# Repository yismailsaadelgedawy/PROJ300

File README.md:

# 32-bit ARM Inspired FPGA Computer

## Introduction

Here, you will find some media to showcase the workings/features of the project.
For detail on how all of this works, see my LinkedIn profile post at: [https://www.linkedin.com/in/youssef-el-geddawy-ab2085292/](https://www.linkedin.com/feed/update/urn:li:activity:7228014319110664192/)

### Overall System Running

https://github.com/user-attachments/assets/22ee120e-133d-488a-b780-022c8d299afa

Green LEDs: general purpose registers, r0-r12.
Red LEDs: memory mapped registers.

The assembly program running is the following:

```
str(0x01, vga_sel); // manual rendering mode
mov(r0, 0x000); // r0 init - colour data
str(0, tmr); // make sure timer is stopped
str(r0, vga_colour);
str(70, tmr); // tmr start 70ms
ldr(r1, "[]", tmr); // tmr state
cmp(r1, 1); // is timer done
beq(9); // if
b(5); // else
add(r0, r0,1);   
add(r1, r1,2);   
add(r2, r2,3);   
add(r3, r3,7);   
add(r4, r4,15);   
add(r5, r5,31);   
add(r6, r6,63);   
add(r7, r7,127);   
add(r8, r8,255);   
add(r9, r9,511);
add(r10, r10,1023);
add(r11, r11,2047);
add(r12, r12,4095);
str(r0, led); // leds on
b(2); // back to start

// showcase program //
```

### Keyboard Piano

https://github.com/user-attachments/assets/b63c3ae4-20a9-44ec-8537-4e127ff7aa50

The assembly program running is the following:

```
str(0x01, vga_sel); // manual rendering mode
ldr(r0, "[]", keyboard_input); // read key pressed
cmp(r0, 0x1C); // A
beq(5); // if
b(13); // else
str(0x1C, audio); // A note
str(0xF00, vga_colour); // red
ldr(r0, "[]", keyboard_input); // read key pressed
cmp(r0, 0x00); // key released
beq(11); // if
b(7); // else
str(0x00, audio); // tune off
str(0x00, vga_colour); // display off
cmp(r0, 0x32); // B
beq(16); // if
b(24); // else
str(0x32, audio); // B note
str(0xE80, vga_colour); // orange
ldr(r0, "[]", keyboard_input); // read key pressed
cmp(r0, 0x00); // key released
beq(22); // if
b(18); // else
str(0x00, audio); // tune off
str(0x00, vga_colour); // display off
cmp(r0, 0x21); // C
beq(27); // if
b(35); // else
str(0x21, audio); // C note
str(0xFF0, vga_colour); // yellow
ldr(r0, "[]", keyboard_input); // read key pressed
cmp(r0, 0x00); // key released
beq(33); // if
b(29); // else
str(0x00, audio); // tune off
str(0x00, vga_colour); // display off
cmp(r0, 0x23); // D
beq(38); // if
b(46); // else
str(0x23, audio); // D note
str(0x0F0, vga_colour); // green
ldr(r0, "[]", keyboard_input); // read key pressed
cmp(r0, 0x00); // key released
beq(44); // if
b(40); // else
str(0x00, audio); // tune off
str(0x00, vga_colour); // display off
cmp(r0, 0x24); // E
beq(49); // if
b(57); // else
str(0x24, audio); // E note
str(0x00F, vga_colour); // blue
ldr(r0, "[]", keyboard_input); // read key pressed
cmp(r0, 0x00); // key released
beq(55); // if
b(51); // else
str(0x00, audio); // tune off
str(0x00, vga_colour); // display off
cmp(r0, 0x2B); // F
beq(60); // if
b(68); // else
str(0x2B, audio); // F note
str(0xB3E, vga_colour); // indigo
ldr(r0, "[]", keyboard_input); // read key pressed
cmp(r0, 0x00); // key released
beq(66); // if
b(62); // else
str(0x00, audio); // tune off
str(0x00, vga_colour); // display off
cmp(r0, 0x34); // G
beq(71); // if
b(1); // else
str(0x34, audio); // G note
str(0x83F, vga_colour); // violet
ldr(r0, "[]", keyboard_input); // read key pressed
cmp(r0, 0x00); // key released
beq(77); // if
b(73); // else
str(0x00, audio); // tune off
str(0x00, vga_colour); // display off
b(1);

// showcase program //
```

### Hardware Timers and Blinky

https://github.com/user-attachments/assets/cfb77016-71fe-4d39-8311-53863db17fb7

The assembly program running is the following:

```
str(0x00, led); // LEDs off initially
str(100, tmr); // start 100ms tmr
ldr(r0, "[]", tmr); // timer state
cmp(r0, 0x01);  // if done
beq(6); // if
b(2); // else
str(0xFF, led); // LEDs on
str(0x00, tmr); // stop tmr;
str(100, tmr); // start 100ms timer
ldr(r0, "[]", tmr); // timer state
cmp(r0, 0x01);  // if done
beq(13); // if
b(9); // else
str(0x00, led); // LEDs off
str(0x00, tmr); // stop tmr;
b(1);

```

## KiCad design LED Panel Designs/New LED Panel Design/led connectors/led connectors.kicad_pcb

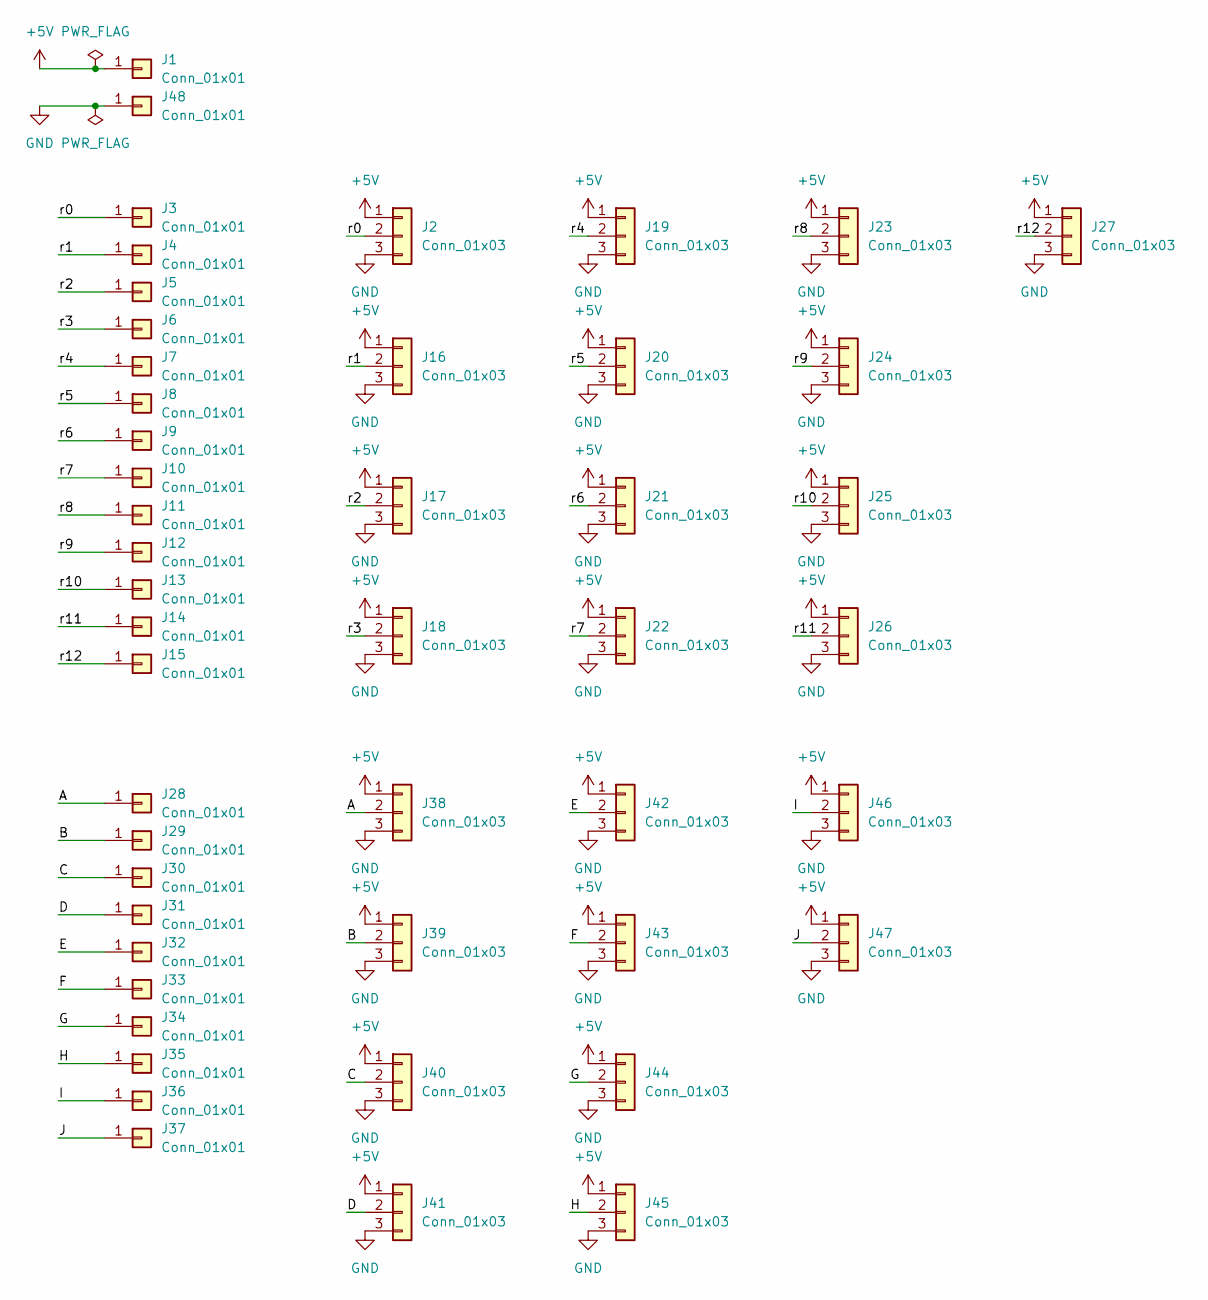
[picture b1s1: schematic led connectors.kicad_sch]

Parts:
J1, J3, J4, J5, J6, J7, J8, J9, J10, J11, J12, J13, J14, J15, J28, J29, J30, J31, J32, J33, J34, J35, J36, J37, J48: Conn_01x01; PinHeader_1x01_P2.54mm_Vertical
J2, J16, J17, J18, J19, J20, J21, J22, J23, J24, J25, J26, J27, J38, J39, J40, J41, J42, J43, J44, J45, J46, J47: Conn_01x03; JST_XH_B3B-XH-A_1x03_P2.50mm_Vertical

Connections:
+5V: J1.1, J2.1, J16.1, J17.1, J18.1, J19.1, J20.1, J21.1, J22.1, J23.1, J24.1, J25.1, J26.1, J27.1, J38.1, J39.1, J40.1, J41.1, J42.1, J43.1, J44.1, J45.1, J46.1, J47.1
/A: J28.1, J38.2
/B: J29.1, J39.2
/C: J30.1, J40.2
/D: J31.1, J41.2
/E: J32.1, J42.2
/F: J33.1, J43.2
/G: J34.1, J44.2
/H: J35.1, J45.2
/I: J36.1, J46.2
/J: J37.1, J47.2
/r0: J2.2, J3.1
/r1: J4.1, J16.2
/r2: J5.1, J17.2
/r3: J6.1, J18.2
/r4: J7.1, J19.2
/r5: J8.1, J20.2
/r6: J9.1, J21.2
/r7: J10.1, J22.2
/r8: J11.1, J23.2
/r9: J12.1, J24.2
/r10: J13.1, J25.2
/r11: J14.1, J26.2
/r12: J15.1, J27.2
GND: J2.3, J16.3, J17.3, J18.3, J19.3, J20.3, J21.3, J22.3, J23.3, J24.3, J25.3, J26.3, J27.3, J38.3, J39.3, J40.3, J41.3, J42.3, J43.3, J44.3, J45.3, J46.3, J47.3, J48.1

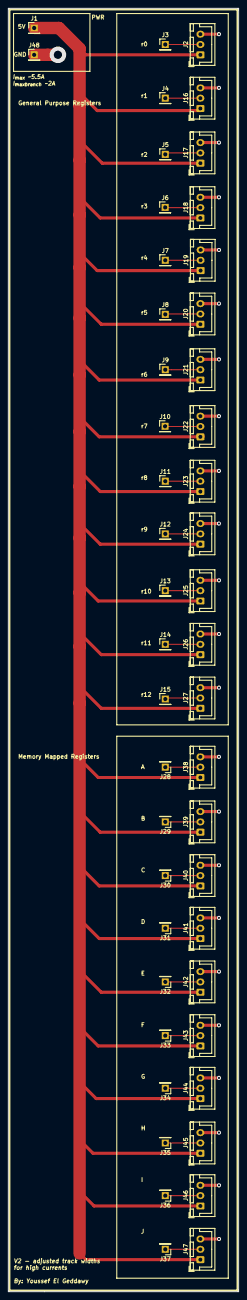
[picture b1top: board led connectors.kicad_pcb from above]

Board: 2 copper layers, 55.8 x 310.8 mm, 48 parts (0 on the bottom side), 25 nets.

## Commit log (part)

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2024-01-21 Initial file setup
2024-01-22 SD card folder
    (maybe I will do it - who knows)
2024-01-24 created LEDs folder
2024-01-30 finished hsync and vsync counters
    also added quartus project files
2024-01-30 quartus pin setup and schematic
2024-01-30 RGB controller v1 done
2024-01-31 sprite ROMs and RGB controller v2
2024-01-31 Multiple sprite support added
2024-01-31 neatened schematic
2024-01-31 added comments on schematic
2024-01-31 added comments; removed unneeded code
2024-02-01 added pixel offsets
    using signed arithmetic now
2024-02-01 removed redundant signed types
2024-02-01 adjusted bit widths to accommodate sign bit
2024-02-01 adjustments in bit widths
    will add sprite movement according to user input later -- so far sprite offsets are hardwired into the silicon
2024-02-01 created audio controller folder
2024-02-02 [NOT WORKING] attempt at code optimisation
2024-02-02 buttons move sprites now!
2024-02-02 folder name change
2024-02-02 Added Block Diagram.drawio
2024-02-02 updated block diagram
2024-02-02 added edge detection
    uses a nifty 4-pixel mechanism
2024-02-02 VGA controller complete (for now)
    tidied up schematic files
2024-02-03 neatened schematic + comments
2024-02-04 added fine tuned clock divider
    can take any frequency from 1Hz to 25MHz
2024-02-04 optimised code
    combined outputs into busses - cleaner!
2024-02-04 commented schematic
2024-02-06 created ps2 modules
    keyboard is not working; cannot test yet
2024-02-06 [BUG] ps2 module
    * added seven segment display to help debug
    * simulated holding down the same key in the tb
    * ps2 controller bugs out when holding down the same key - will fix later
2024-02-06 updated testbench for ps2 controller
2024-02-06 [BUG FIX] ps2 data no longer shifts
    *still another bug left to squash (latching issue)
2024-02-06 schematic update
2024-02-07 fixed all PS2 bugs
    works perfectly now!
2024-02-08 audio controller v1 done
    still barebones; not very well written imo
2024-02-08 added keyboard key detector
    untested still
2024-02-08 added audio files and key release detection
2024-02-09 [NOT WORKING] merged keyboard with audio controller
    will fix later
2024-02-09 adjusted bus width and frequencies
2024-02-09 [FIX] keyboard audio works now
    even sharp notes work!
2024-02-09 added lower octave switch
2024-02-09 added comments and updated schematics
2024-02-14 [UNTESTED] created UART modules
    * software to send a character on UART2
    * firmware UART components
2024-02-14 [BUG] wired up UART modules
    deadlock via "transmission_state" wire!!!!
    will fix later
2024-02-14 [FIX] UART fully working now
    still need to think about CDC...
2024-02-14 updated UART schematic
2024-02-16 added debouncer and debug address counter
    the button and its address counter will be used for instruction debugging later!
2024-02-16 renamed modules for clarity
2024-02-16 [UNTESTED] instruction RAM v1 completed
    still need to add a CPU random access fetch mode later
2024-02-16 added random access fetch template code
2024-02-17 [NOT WORKING] initial testing of RAM
2024-02-17 [NOT WORKING] almost there with RAM...
2024-02-17 removed redundant comments
2024-02-17 many bug fixes and additions
    * fixed instruction RAM
    * added variable read frequency parameter to RAM
    * add CDC via double flopping from UART to RAM
2024-02-21 added CPU design files
2024-02-21 Added ISA descriptions
2024-02-21 optimised instruction RAM
    removed FIFO read mode - unnecessary.; replaced with random access fetch (for the CPU)
    ALM utilisation went down from 10% -> 7%
2024-02-21 Reduced max number of instructions in RAM
    Reduction from 255 instructions to 100.
    Important as cannot infer BRAM.
    ALM utilisation reduced from 7% -> 4%
2024-02-22 created individual CPU components
    haven't tested them as a whole yet, just individual tests for now
2024-02-22 [async problem] connections + many bug fixes
    working in simulation but not IRL;
    asynchronous problem;
    will have to find an alternative
2024-02-23 [BUG FIX] fixed CPU
    works fine now!
    found an alternative to asynchronous load!
2024-02-23 made instructions more readable
    concatenation!
2024-02-23 added schematic comments
2024-02-28 added some arm assembly
    to approximate my CPU architecture and ISA
2024-02-28 commented the assembly
    includes utilisation
2024-02-28 started designed ISA
2024-02-28 updated ISA
2024-02-28 refined ISA
2024-02-29 draft execution routines
2024-03-01 updated ISA file
    * modified routines
    * added control signal logic
2024-03-13 MAJOR ISA update
2024-03-13 added MEMLOAD as control line in ISA
    architecture now includes bidirectional data!
2024-03-18 started coding complex CPU modules
    * ALU
    * BUS MUX
    * CU counter and decoder
    * CU logic WIP
    also fixed a few ISA bugs
2024-03-19 Update CU_logic.sv
    added control signals for most states
    a few more to go
2024-03-19 [UNTESTED] completed CU logic
    will testbench it and verify it works later!
2024-03-19 testbenched CU logic module
    all good!
2024-03-20 built NZCV logic module
    the CPU has flags now!
2024-03-20 added testbench automation using do file
    handy!
2024-03-20 added do file for CU_logic module
2024-03-21 GPR and operand selectors completed
    tested as well!
2024-03-21 added do file for GPR circuit
2024-03-21 cleaned up the do file
    uses a wildcard instead :)
2024-03-22 [HALF-TESTED] completed memory modules
    * tested all individually - pass
    * yet to test them all together
    this is regarding the encapsulation of the instruction, memory mapped regs and stack memories
2024-03-22 edited quartus files
2024-03-23 fully connected and tested memory modules
    * memory now completed
    * passes all tests
2024-03-23 made tests more rigorous; renamed files
    * encapsulated the concatenator and the rest of the GPR selection circuitry - more readable
    * renamed files to be more sensical
    * added assertions to GPR_selector_tb to make the test more rigorous!
2024-03-23 fixed comment
2024-03-23 added guide comment in case
2024-03-24 preparing CPU for testing
    * wired CPU
    * started writing instructions in test ROM
    ** major oversight discovered in AL operations; will work on a compensation mechanism later
2024-03-24 improved testing methodology
    * shown in one file
    * only display errors; use an error flag and a print statement at the end if all tests passed or not!
2024-03-25 [MAJOR UPDATE] bug fixes + module changes
    * fixed many connection errors in the schematic
    * fixed bug in CU_logic where cmp1 was missing COUNTER_CLR to go back to the fetch1 state
    * modified des_reg_selector to allow rop2 bits to pass through in the ALTMOV1 state
    * made flags_setter from FF->latch (fixes bugs)
    * modified testROM cmp instructions to be more useful in testing
    * changed some module semantics including:
2024-03-25 removed asyncrohnous logic
    replaced all asynchronous flip-flops with latches instead; (regarding the 4 registers mentioned in the previous commit)
2024-03-26 [MAJOR UPDATE] CPU completed!
    * fixed ALU bug
    * tested all possible instructions (found din testROM)
    * all tests pass!
2024-03-27 started modelling IC components
    needed for LED panel to display all the internal registers
2024-03-28 simplified circuit
    now uses counter value rather than the placeholder FF chain before
2024-03-28 more accurate model of logic gates using ICs
2024-03-28 continued modelling FPGA and PCB circuitry
    lots of timing issues for now...
2024-03-28 kind of remedied timing issues
    dev1 is fine
    dev2 2 cycles off
    consider adding ff chain on ill devices
    also MSB and LSB are reversed...
2024-03-28 fixed most of the timing issues and squashed bugs
2024-03-28 more accurate model for CD4024 IC
    counts on falling edge, not rising
2024-03-28 finished modelling approximation
    :)
2024-03-29 optimised IC usage
    huge reduction in ICs
2024-03-29 removed redundant connections in LED panel model
2024-03-29 removed redundant stuff...
    * removed "load" input from the PSSR
    * removed asynchronous logic from the FPGA counter to avoid synthesis problems
2024-03-29 removed more redundant code
    also updated schematic symbols
2024-03-29 finalised BOM for LED panel
2024-03-30 Huge optimisation in number of gates
    * this concerns the led_controller32
    * will fix AND bug later...
2024-04-01 created modified instruction RAM
    to accomodate 38-bit instruction word...
    fully tested - passes!
2024-04-02 improvements in UART module
    * better code for bsy_detector: always_latch construct (removed asynch logic) + eot flag to be used with CPU programming later - speeds ups programming as we no longer need the special byte '$' to in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
    * added bsy_detector_tb
2024-04-02 added a few things...
    * added schematic files to repo along with some info.txt files for context
    * added provisional list of memory mapped registers in "\Complex CPU\sv files\Memory Map.txt" - will add more (especially for VGA stuff) but will start simple for now...
2024-04-02 started writing assembler
2024-04-03 [UNTESTED] finished writing the assembly instructions
    * will test later
    N.B. do not forget to test UART with new RAM (removal of '$' character)
2024-04-03 fully tested assembler + squashed bugs
2024-04-03 [UNFINISHED] heavy RAM modifications
    removed modified version - did not work
    modifying the one I had originally, not done yet
2024-04-03 Revert "[UNFINISHED] heavy RAM modifications"
    This reverts commit 8eb56f6e19c35ef8c20a848ad4e00660b27ba054.
2024-04-04 [MAJOR UPDATE] instruction RAM semantics change
    * no longer needs special char
    * uses eot flag (stop bit) instead
    * lowered delay from 100ms to 10ms
    * much faster programming times!
2024-04-04 instruction RAM fully completed now
    finally...
2024-04-04 made instructionrandom access fetch asynch
    // this MUST be asynchronous to the clock
    // the CPU is an a faster clock domain (25MHz-50MHz)!
2024-04-04 packaged CPU into symbol
    also created "Full Computer" project file to connect the whole system together...
2024-04-04 added CDC sync chains to instruction buffer
    both @9600Hz but still different domains (different phases)
2024-04-05 connected all peripherals to CPU and memory
    will try to re-write UART buffer to infer BRAM to lower resource usage since I recieve an error regarding exceeding register usage...
2024-04-06 Revert "connected all peripherals to CPU and memory"
    This reverts commit 94ccdf902c28e4ceefb542f5ab92d4fcdbdd2ac6.
2024-04-06 [MAJOR UPDATE] wired the computer!
    tested a few instructions and it works (so far!)!!!
2024-04-07 [MAJOR UPDATE]
    squashed many many bugs...
    wrote a few example programs;
    everything works!
2024-04-08 additions to CPU
    * added hardware timer support
    * added slide switch support
    * wrote more example programs
2024-04-09 added asynch rst for instruction RAM
    synthesises properly yay!
2024-04-10 wrote WS2812B controller
    works!
    (will improve it later)
2024-04-10 modified controller
    added colour parameter
    added module in quartus; synthesises!
    * will try when PCB is assembled
2024-04-10 added important syntax-related comment
2024-04-11 started writing dissertation
    up until research section completed
2024-04-15 added numbering to instruction testbench
2024-04-19 fixed protocol glitches
2024-04-19 connected LED panel testbench
    works!
    * will connect to CPU registers later
2024-04-20 adjusted WS2812B timings
2024-04-20 wired LED panel to CPU
2024-04-20 UART pin change
    uses pinK16 now
    other pins did not work not sure why
2024-04-25 made assembler much more power efficient!
2024-04-29 Dissertation Completed
2024-04-29 added gantt chart to dissertation
2024-04-29 fixed formatting
2024-04-30 Updated schematic and example program
2024-10-22 created README with project showcase!
